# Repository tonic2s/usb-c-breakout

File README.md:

# usb-c-breakout
 Simple usb-c breakoutboard with 5k1 cc resistors

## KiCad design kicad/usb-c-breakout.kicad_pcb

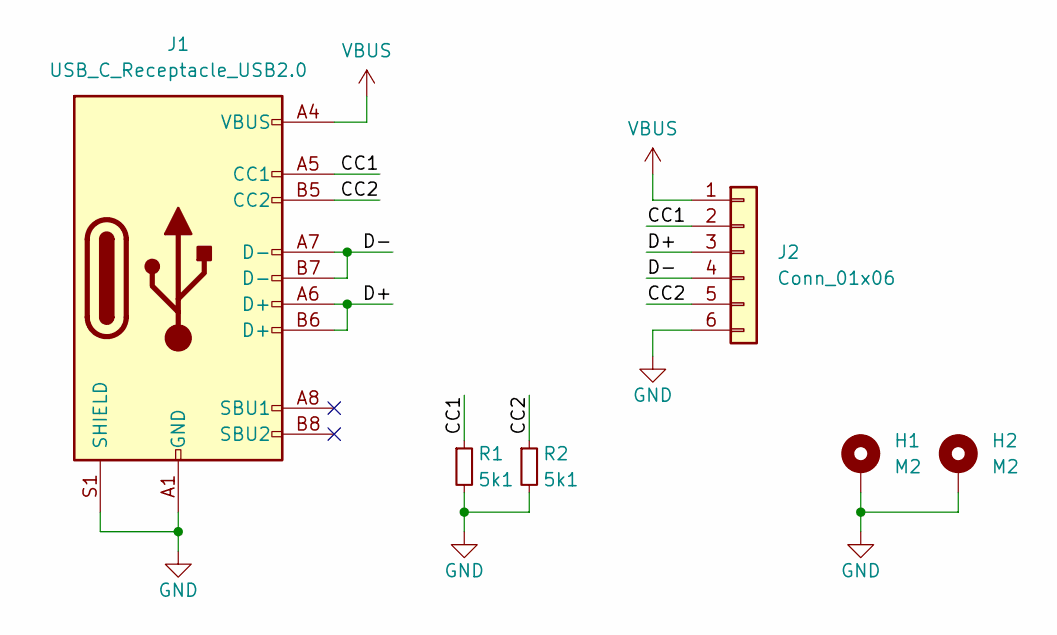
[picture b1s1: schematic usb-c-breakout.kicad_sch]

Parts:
H1, H2: M2; MountingHole_2.2mm_M2_DIN965_Pad
J1: USB_C_Receptacle_USB2.0; USB_C_Receptacle_GCT_USB4085; Mouser No 640-USB4085-GF-A
J2: Conn_01x06; PinHeader_1x06_P2.54mm_Vertical; Mouser No 523-G800W302018EU
R1, R2: 5k1; R_Axial_DIN0204_L3.6mm_D1.6mm_P5.08mm_Horizontal; Mouser No 594-5063JD5K100FT

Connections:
/CC1: J1.A5 (CC1), J2.2, R1.1
/CC2: J1.B5 (CC2), J2.5, R2.1
/D+: J1.A6 (D+), J1.B6 (D+), J2.3
/D-: J1.A7 (D-), J1.B7 (D-), J2.4
GND: H1.1, H2.1, J1.A1 (GND), J1.A12 (GND), J1.B1 (GND), J1.B12 (GND), J1.S1 (SHIELD), J2.6, R1.2, R2.2
VBUS: J1.A4 (VBUS), J1.A9 (VBUS), J1.B4 (VBUS), J1.B9 (VBUS), J2.1

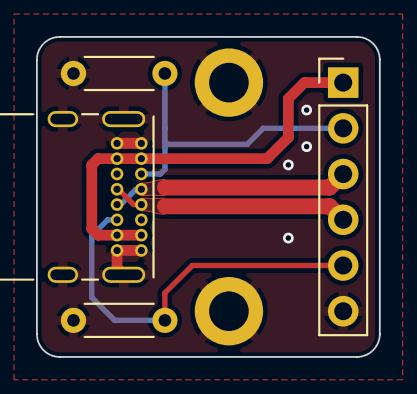
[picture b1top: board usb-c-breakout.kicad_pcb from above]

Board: 2 copper layers, 19.0 x 17.8 mm, 6 parts (0 on the bottom side), 6 nets.
